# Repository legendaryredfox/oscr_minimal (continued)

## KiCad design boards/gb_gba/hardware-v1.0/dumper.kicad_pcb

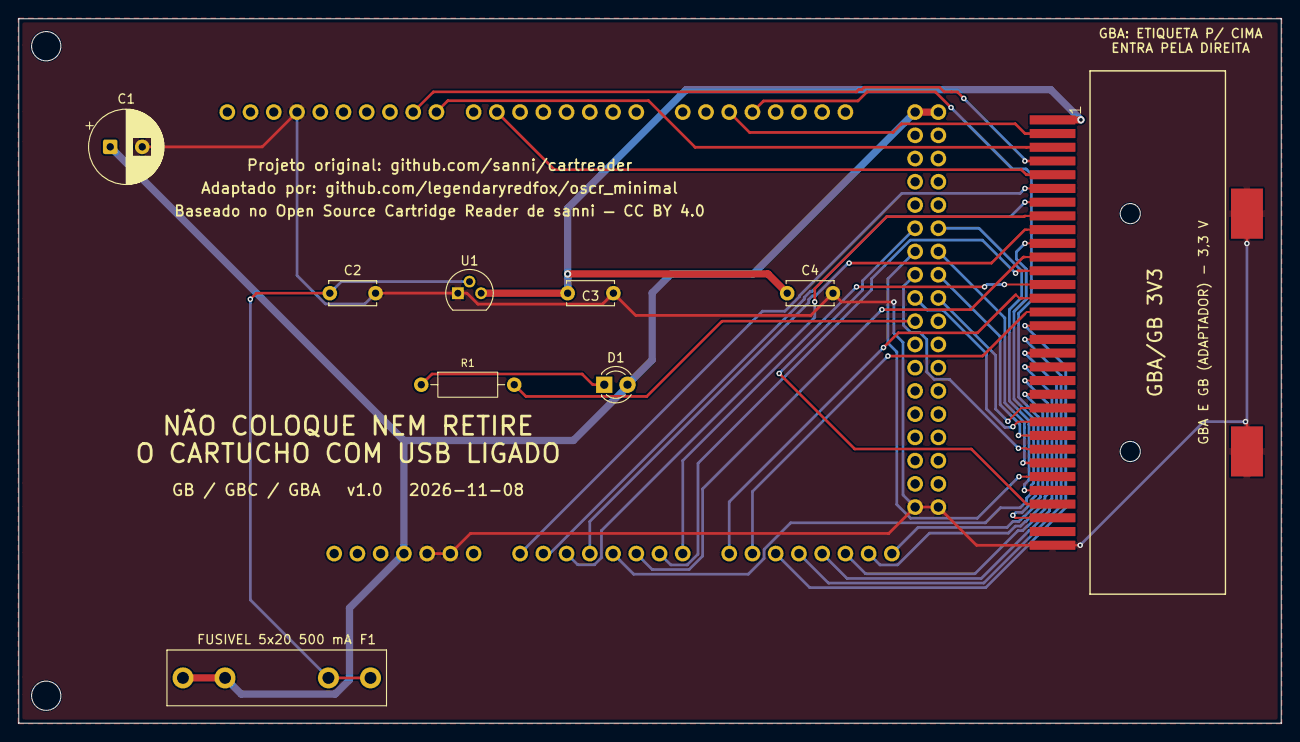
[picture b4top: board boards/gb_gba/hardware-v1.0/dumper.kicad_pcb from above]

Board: 2 copper layers, 138.0 x 77.0 mm, 12 parts (0 on the bottom side), 35 nets.

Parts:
A1: Mega2560_R3_Shield
C1: 470u/16V; CP_Radial_D8.0mm_P3.50mm
C2, C3: 1u; C_Disc_D5.0mm_W2.5mm_P5.00mm
C4: 100n; C_Disc_D5.0mm_W2.5mm_P5.00mm
D1: LED 3mm; LED_D3.0mm
F1: Fusivel 5x20 500mA; Fuseholder_Littelfuse_100_series_5x20mm
GBA1: GBA_Slot
MH1, MH3: MountingHole_3.2mm; MountingHole_3.2mm_M3
R1: 220R; R_Axial_DIN0207_L6.3mm_D2.5mm_P10.16mm_Horizontal
U1: MCP1700-3302E/TO (3,3 V); TO-92

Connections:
+3V3: C3.1, C4.1, GBA1.1, U1.3
+5V: A1.5V1, A1.5V3, A1.5V4, C1.1, D1.2, F1.1
+5V_CART: C2.1, F1.2, U1.2
/A0: A1.A0, GBA1.6
/A1: A1.A1, GBA1.7
/A2: A1.A2, GBA1.8
/A3: A1.A3, GBA1.9
/A4: A1.A4, GBA1.10
/A5: A1.A5, GBA1.11
/A6: A1.A6, GBA1.12
/A7: A1.A7, GBA1.13
/A8: A1.A8, GBA1.14
/A9: A1.A9, GBA1.15
/A10: A1.A10, GBA1.16
/A11: A1.A11, GBA1.17
/A12: A1.A12, GBA1.18
/A13: A1.A13, GBA1.19
/A14: A1.A14, GBA1.20
/A15: A1.A15, GBA1.21
/D6: A1.D6, GBA1.5
/D8: A1.D8, GBA1.3
/D9: A1.D9, GBA1.4
/D16: A1.D16, GBA1.2
/D17: A1.D17, GBA1.30
/D30: A1.D30, GBA1.29
/D31: A1.D31, GBA1.28
/D32: A1.D32, GBA1.27
/D33: A1.D33, GBA1.26
/D34: A1.D34, GBA1.25
/D35: A1.D35, GBA1.24
/D36: A1.D36, GBA1.23
/D37: A1.D37, GBA1.22
GND: A1.GND1, A1.GND2, A1.GND3, A1.GND5, A1.GND6, C1.2, C2.2, C3.2, C4.2, GBA1.32, GBA1.SHIELD_3, GBA1.SHIELD_4, U1.1
unnamed: A1.D38, R1.2
unnamed: D1.1, R1.1

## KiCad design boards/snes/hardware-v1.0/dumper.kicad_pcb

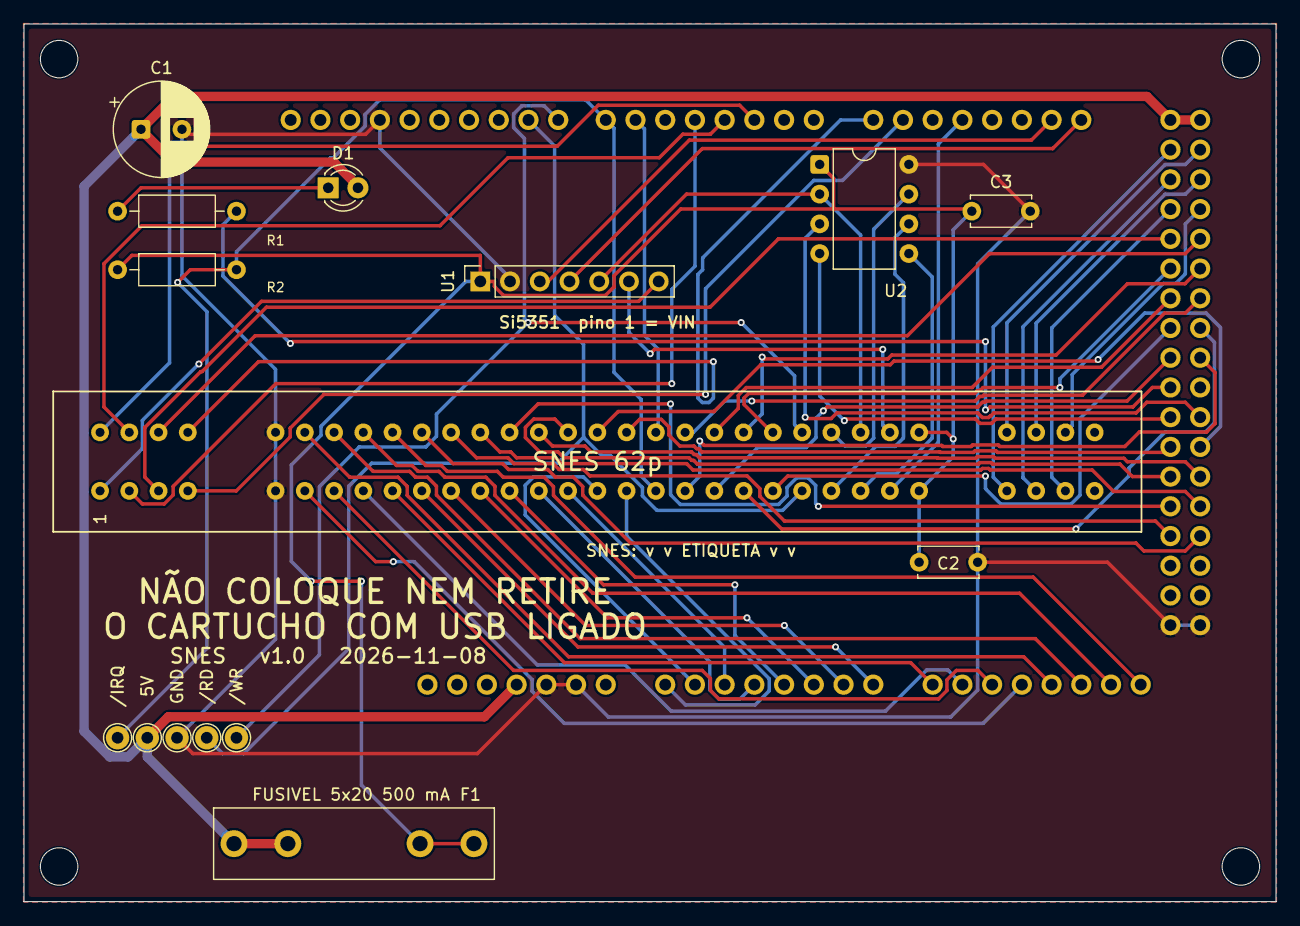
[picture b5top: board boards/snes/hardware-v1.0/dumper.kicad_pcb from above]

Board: 2 copper layers, 107.0 x 75.0 mm, 20 parts (0 on the bottom side), 65 nets.

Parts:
A1: Mega2560_R3_Shield
C1: 470u/16V; CP_Radial_D8.0mm_P3.50mm
C2, C3: 100n; C_Disc_D5.0mm_W2.5mm_P5.00mm
D1: LED 3mm; LED_D3.0mm
F1: Fusivel 5x20 500mA; Fuseholder_Littelfuse_100_series_5x20mm
MH1, MH2, MH3, MH4: MountingHole_3.2mm; MountingHole_3.2mm_M3
R1: 220R; R_Axial_DIN0207_L6.3mm_D2.5mm_P10.16mm_Horizontal
R2: 1k; R_Axial_DIN0207_L6.3mm_D2.5mm_P10.16mm_Horizontal
SNES1: SNES_Slot
TP1: 5V; TestPoint_THTPad_D2.0mm_Drill1.0mm
TP2: GND; TestPoint_THTPad_D2.0mm_Drill1.0mm
TP3: /RD; TestPoint_THTPad_D2.0mm_Drill1.0mm
TP4: /WR; TestPoint_THTPad_D2.0mm_Drill1.0mm
TP5: /IRQ; TestPoint_THTPad_D2.0mm_Drill1.0mm
U1: Si5351_Module; PinSocket_1x07_P2.54mm_Vertical
U2: PIC12F629 (em soquete; snescic-lock-resync); DIP-8_W7.62mm

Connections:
+5V: A1.5V1, A1.5V3, A1.5V4, C1.1, D1.2, F1.1, TP1.1
+5V_CART: C2.1, C3.1, F1.2, R2.1, SNES1.27, SNES1.58, U1.1, U2.1
/A0: A1.A0, SNES1.17
/A1: A1.A1, SNES1.16
/A2: A1.A2, SNES1.15
/A3: A1.A3, SNES1.14
/A4: A1.A4, SNES1.13
/A5: A1.A5, SNES1.12
/A6: A1.A6, SNES1.11
/A7: A1.A7, SNES1.10
/A8: A1.A8, SNES1.9
/A9: A1.A9, SNES1.8
/A10: A1.A10, SNES1.7
/A11: A1.A11, SNES1.6
/A12: A1.A12, SNES1.37
/A13: A1.A13, SNES1.38
/A14: A1.A14, SNES1.39
/A15: A1.A15, SNES1.40
/CIC_DATA_0: SNES1.55, U2.7
/CIC_DATA_1: SNES1.24, U2.6
/CIC_RESET: SNES1.25, U2.5
/CLK0: SNES1.1, U1.7
/CLK1: SNES1.57, U1.6
/CLK2: SNES1.56, U1.5, U2.2
/D2: A1.D2, SNES1.32
/D3: A1.D3, SNES1.33
/D4: A1.D4, SNES1.2
/D6: A1.D6, SNES1.49
/D7: A1.D7, R2.2, SNES1.18, TP5.1
/D8: A1.D8, SNES1.54, TP4.1
/D9: A1.D9, SNES1.23, TP3.1
/D14: A1.D14, SNES1.35
/D15: A1.D15, SNES1.4
/D17: A1.D17, SNES1.26
/D22: A1.D22, SNES1.28
/D23: A1.D23, SNES1.59
/D24: A1.D24, SNES1.29
/D25: A1.D25, SNES1.60
/D26: A1.D26, SNES1.30
/D27: A1.D27, SNES1.61
/D28: A1.D28, SNES1.3
/D29: A1.D29, SNES1.34
/D30: A1.D30, SNES1.53
/D31: A1.D31, SNES1.52
/D32: A1.D32, SNES1.51
/D33: A1.D33, SNES1.50
/D34: A1.D34, SNES1.22
/D35: A1.D35, SNES1.21
/D36: A1.D36, SNES1.20
/D37: A1.D37, SNES1.19
/D42: A1.D42, SNES1.48
/D43: A1.D43, SNES1.47
/D44: A1.D44, SNES1.46
/D45: A1.D45, SNES1.45
/D46: A1.D46, SNES1.44
/D47: A1.D47, SNES1.43
/D48: A1.D48, SNES1.42
/D49: A1.D49, SNES1.41
GND: A1.GND1, A1.GND2, A1.GND3, A1.GND5, A1.GND6, C1.2, C2.2, C3.2, SNES1.5, SNES1.36, TP2.1, U1.2, U2.8
unnamed: A1.D38, R1.2
unnamed: D1.1, R1.1
unnamed: A1.D21, U1.4
unnamed: A1.D20, U1.3
unnamed: A1.D40, U2.4
unnamed: A1.D41, U2.3

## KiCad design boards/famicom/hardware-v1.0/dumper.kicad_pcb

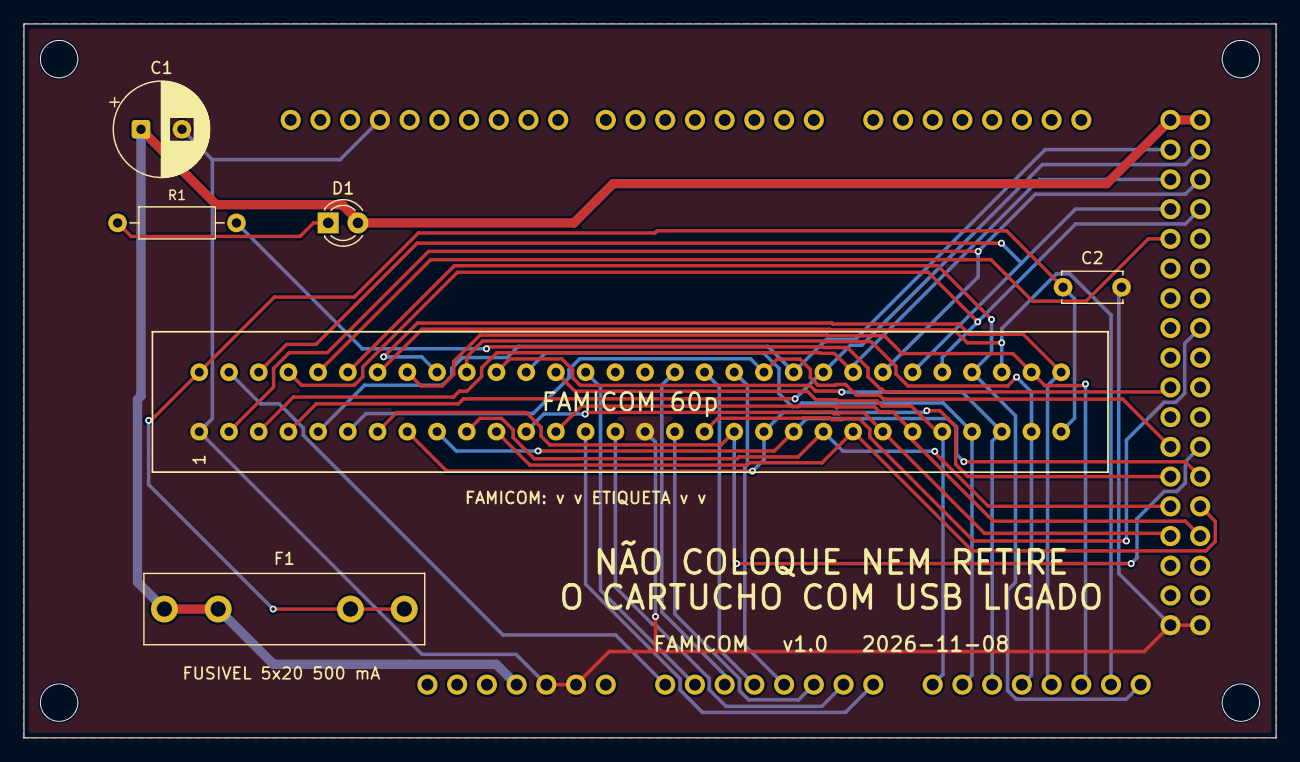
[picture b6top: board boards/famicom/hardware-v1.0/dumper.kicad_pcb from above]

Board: 2 copper layers, 107.0 x 61.0 mm, 11 parts (0 on the bottom side), 37 nets.

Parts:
A1: Mega2560_R3_Shield
C1: 470u/16V; CP_Radial_D8.0mm_P3.50mm
C2: 100n; C_Disc_D5.0mm_W2.5mm_P5.00mm
D1: LED 3mm; LED_D3.0mm
F1: Fusivel 5x20 500mA; Fuseholder_Littelfuse_100_series_5x20mm
FC1: FC_Slot
MH1, MH2, MH3, MH4: MountingHole_3.2mm; MountingHole_3.2mm_M3
R1: 220R; R_Axial_DIN0207_L6.3mm_D2.5mm_P10.16mm_Horizontal

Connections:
+5V: A1.5V1, A1.5V3, A1.5V4, C1.1, D1.2, F1.1
+5V_CART: C2.1, F1.2, FC1.30, FC1.31
/A0: A1.A0, FC1.32
/A1: A1.A1, FC1.44
/A2: A1.A2, FC1.47
/A3: A1.A3, FC1.48
/A4: A1.A4, FC1.49
/A5: A1.A5, FC1.17
/A6: A1.A6, FC1.15
/A7: A1.A7, FC1.14
/A8: A1.A8, FC1.26, FC1.43
/A9: A1.A9, FC1.27, FC1.42
/A10: A1.A10, FC1.28, FC1.41
/A11: A1.A11, FC1.29, FC1.40
/A12: A1.A12, FC1.39, FC1.60
/A13: A1.A13, FC1.38, FC1.59
/A14: A1.A14, FC1.37, FC1.58
/A15: A1.A15, FC1.36, FC1.57
/D22: A1.D22, FC1.5, FC1.51
/D23: A1.D23, FC1.4, FC1.52
/D24: A1.D24, FC1.3, FC1.53
/D25: A1.D25, FC1.2, FC1.54
/D26: A1.D26, FC1.33, FC1.55
/D27: A1.D27, FC1.34, FC1.56
/D28: A1.D28, FC1.35
/D35: A1.D35, FC1.18
/D42: A1.D42, FC1.6, FC1.50
/D43: A1.D43, FC1.7, FC1.19
/D44: A1.D44, FC1.8, FC1.20
/D45: A1.D45, FC1.9, FC1.21
/D46: A1.D46, FC1.10, FC1.22
/D47: A1.D47, FC1.11, FC1.23
/D48: A1.D48, FC1.12, FC1.24
/D49: A1.D49, FC1.13, FC1.25
GND: A1.GND1, A1.GND2, A1.GND3, A1.GND5, A1.GND6, C1.2, C2.2, FC1.1, FC1.16
unnamed: A1.D38, R1.2
unnamed: D1.1, R1.1

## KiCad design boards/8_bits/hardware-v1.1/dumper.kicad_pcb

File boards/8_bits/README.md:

# 8_bits — NES, Famicom e Master System

**README por versão** (renders de cima e de baixo, peças, diferenças): [v1.0](hardware-v1.0/README.md), [v1.1](hardware-v1.1/README.md).

Versão mínima de três slots em shield para Arduino Mega 2560 R3, 100% THT, só USB: **NES** (72p, 2,5 mm), **Famicom** (60p, 2,54 mm) e **Master System / Mark III** (50p, 2,54 mm). Os três slots ficam **em paralelo** nos mesmos pinos do Mega (como no `six_slot_adapter` do OSCR): **um cartucho por vez, em um slot só**. Pinagem idêntica ao OSCR HW5 (`docs/pinmap.md`: NES e Famicom da `famicom_nes`, Master System da `megadrive_sms`).

**Si5351, sem PIC:** o NES usa o `CLK0` do Si5351 no pino 37; Famicom e Master System não usam clock (o pino 47 do SMS fica sem ligação, D136). Sem PIC (CIC do SNES), sem R2 e sem regulador de 3,3 V fixo.

## Versões (regra do usuário, 2026-11-11)

- **v1.0: a mínima que funciona, com fusível.** 5V direto nos slots, atrás do F1 (suporte de fusível 5×20 mm de 500 mA, D144). 117,1 × 97,1 mm.
- **v1.1: proteção mais robusta.** A v1.0 mais o seletor de tensão 3,3 V/5 V nos três slots (LDO LD1117V33, Q1 de bypass, Q2 de comando pelo D18; D138, D147) e o J1 "TRAVA 3,3 V". 117,1 × 109,1 mm. Firmware: ambiente `SerialASCII_Volt`.

O 5V dos slots **não é cortado por software** em nenhuma versão (D139): para trocar o cartucho, desligue o USB.

**Estado:** ERC 0 violações; DRC sem ligações abertas nem erros (só avisos de biblioteca); netlist confere com `docs/pinmap.md` nas duas versões (`tools/check_netlist.py --board 8_bits`). Roteadas pelo Freerouting e costuradas com vias de GND: **revisar o layout no KiCad antes de encomendar**. Nada encomendado, montado nem testado.

## Como foi feita (D153)

Criada da `famicom_nes` (v1.0 para a v1.0, v1.1 para a v1.1) com o slot SMS acrescentado, a mesma receita da `megadrive_sms` (D136). Scripts em `tools/boards/8_bits/` (da raiz do repositório):

1. `add_sms_sch.py` acrescenta SMS1 e o capacitor do slot ao esquemático, tira as marcas de não conexão dos 11 pinos do Mega que só o SMS usa (D6, D8, D9, D17, D30 a D34, D36, D37) e põe os rótulos. Variáveis `SMS_VCC` (`+5V_CART` na v1.0, `VCC_CART` na v1.1), `SMS_CAP` e `SMS_CAP_SRC`.
2. `place_sms.py` (python com `pcbnew`) tira trilhas e zonas, acrescenta SMS1 e o capacitor, liga os pads do Mega às nets novas; na v1.0 estende a placa para baixo (127 para 135 mm).
3. `renum.py` (v1.1) e `renum_pwr.py` deixam as referências em sequência: C4 (SMS), C5 e C6 (LDO), R2 a R4, Q1 e Q2, e os `#PWR` (D109, D150).
4. `reroute.sh` (`VER=v1.0|v1.1`): Freerouting, zonas de GND, costura e preenchimento; depois `tools/troca/pads_solidos.py` onde o DRC acusa `starved_thermal`.

```
python3 tools/check_netlist.py --board 8_bits                                              # v1.1
python3 tools/check_netlist.py --board 8_bits boards/8_bits/hardware-v1.0/dumper.kicad_sch  # v1.0
kicad-cli sch erc boards/8_bits/hardware-v1.1/dumper.kicad_sch
kicad-cli pcb drc boards/8_bits/hardware-v1.1/dumper.kicad_pcb
tools/export_fab.sh 8_bits v1.1
```

## Pendências

1. **Direção da etiqueta do cartucho SMS** no silk (não confirmada; NES e Famicom estão).
2. Medidas dos três slots comprados e do módulo Si5351; folga entre o SMS e os furos de canto de baixo (v1.0: 0,3 mm de folga de caixa).
3. **Firmware:** o núcleo `SMS.cpp` está ligado no fork (D137) mas nunca rodou em hardware; o slot SMS desta placa é o `--mapper 0`.
4. Revisar o layout no KiCad (autoroteador).
5. Sem furos de fixação no Mega (só os 4 de canto): a força de inserir o cartucho passa pelos pinos dos headers.

**Peças opcionais:** [`docs/bom.md`](docs/bom.md). BOM: [`docs/bom.md`](docs/bom.md). Montagem: [`docs/montagem.md`](docs/montagem.md).

Atribuição: baseado no Open Source Cartridge Reader de sanni (CC BY 4.0).

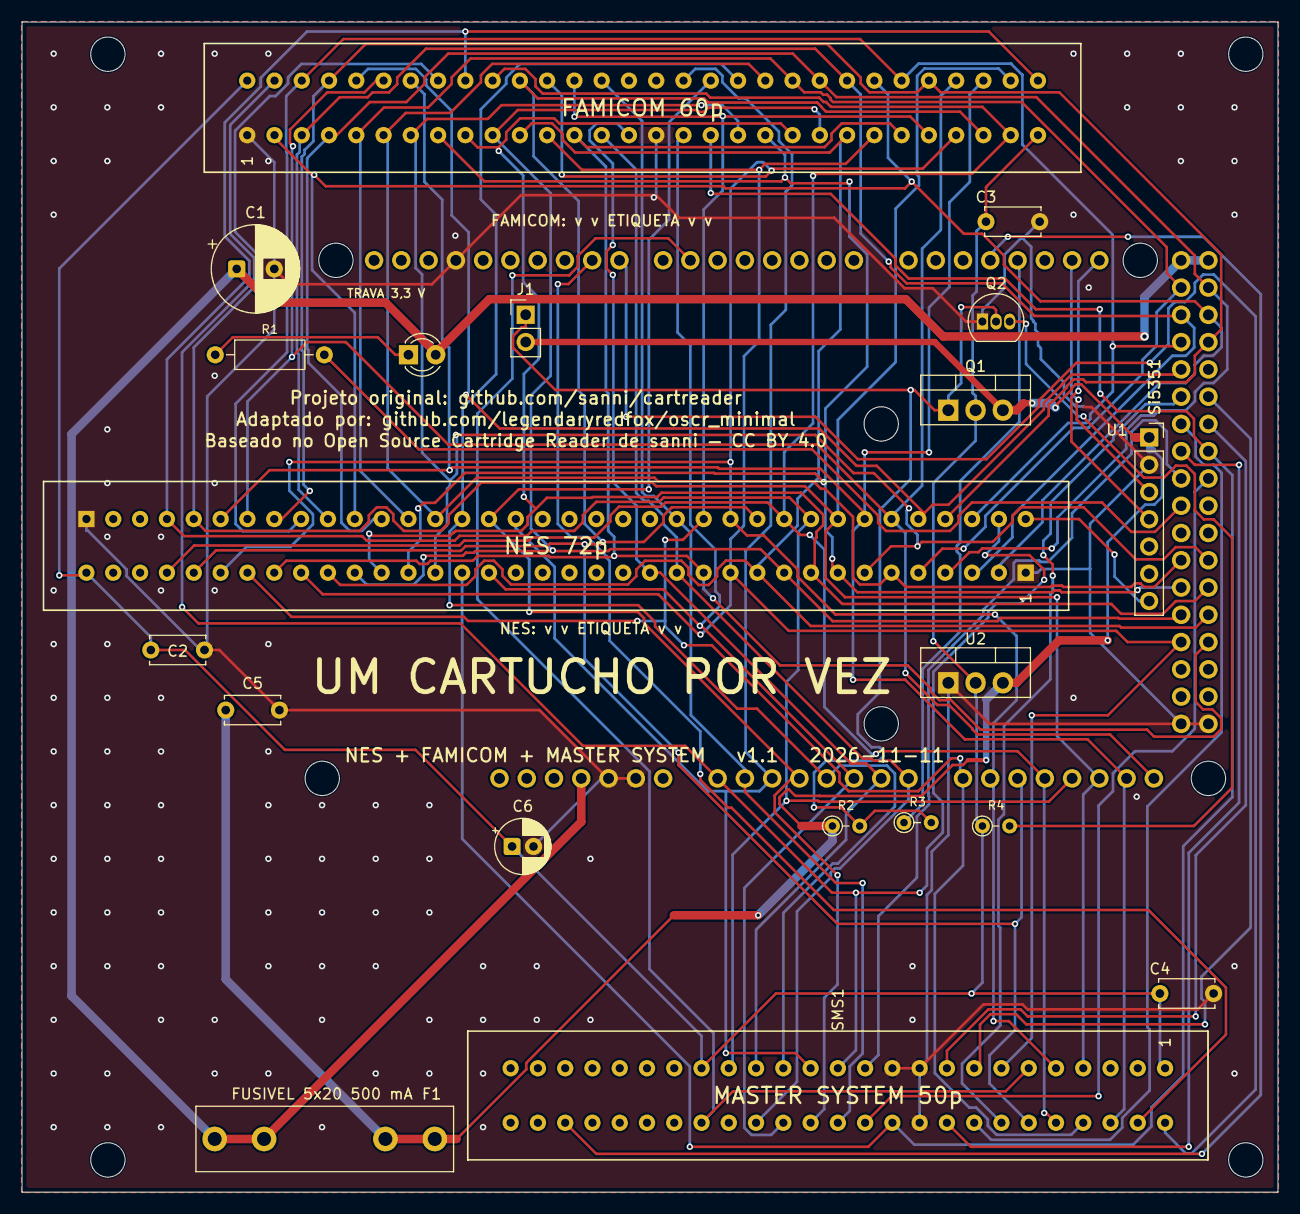
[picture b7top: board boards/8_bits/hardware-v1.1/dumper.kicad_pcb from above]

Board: 2 copper layers, 117.0 x 109.0 mm, 25 parts (0 on the bottom side), 55 nets.

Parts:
A1: Mega2560_R3_Shield
C1: 470u/16V; CP_Radial_D8.0mm_P3.50mm
C2, C3, C4, C5: 100n; C_Disc_D5.0mm_W2.5mm_P5.00mm
C6: 10u/16V; CP_Radial_D5.0mm_P2.00mm
D1: LED 3mm; LED_D3.0mm
F1: Fusivel 5x20 500mA; Fuseholder_Littelfuse_100_series_5x20mm
FC1: FC_Slot
J1: TRAVA 3,3 V; PinHeader_1x02_P2.54mm_Vertical
MH1, MH2, MH3, MH4: MountingHole_3.2mm; MountingHole_3.2mm_M3
NES1: NES_Slot
Q1: IRF9540N; TO-220-3_Vertical
Q2: 2N7000; TO-92_Inline
R1: 220R; R_Axial_DIN0207_L6.3mm_D2.5mm_P10.16mm_Horizontal
R2: 100k; R_Axial_DIN0204_L3.6mm_D1.6mm_P2.54mm_Vertical
R3: 1k; R_Axial_DIN0204_L3.6mm_D1.6mm_P2.54mm_Vertical
R4: 220R; R_Axial_DIN0204_L3.6mm_D1.6mm_P2.54mm_Vertical
SMS1: SMS_Slot
U1: Si5351_Module; PinSocket_1x07_P2.54mm_Vertical
U2: LD1117V33; TO-220-3_Vertical

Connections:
+5V: A1.5V1, A1.5V3, A1.5V4, C1.1, D1.2, F1.1
+5V_CART: C5.1, F1.2, J1.2, Q1.3, R2.1, U1.1, U2.3
/A0: A1.A0, FC1.32, NES1.38, SMS1.25
/A1: A1.A1, FC1.44, NES1.50, SMS1.26
/A2: A1.A2, FC1.47, NES1.56, SMS1.27
/A3: A1.A3, FC1.48, NES1.57, SMS1.28
/A4: A1.A4, FC1.49, NES1.58, SMS1.29
/A5: A1.A5, FC1.17, NES1.21, SMS1.30
/A6: A1.A6, FC1.15, NES1.15, SMS1.31
/A7: A1.A7, FC1.14, NES1.14, SMS1.32
/A8: A1.A8, FC1.26, FC1.43, NES1.30, NES1.49, SMS1.8
/A9: A1.A9, FC1.27, FC1.42, NES1.31, NES1.48, SMS1.9
/A10: A1.A10, FC1.28, FC1.41, NES1.32, NES1.47, SMS1.12
/A11: A1.A11, FC1.29, FC1.40, NES1.33, NES1.46, SMS1.10
/A12: A1.A12, FC1.39, FC1.60, NES1.45, NES1.69, SMS1.33
/A13: A1.A13, FC1.38, FC1.59, NES1.44, NES1.68, SMS1.7
/A14: A1.A14, FC1.37, FC1.58, NES1.43, NES1.67, SMS1.6
/A15: A1.A15, FC1.36, FC1.57, NES1.42, NES1.66
/CLK0: NES1.37, U1.7
/D6: A1.D6, SMS1.11, SMS1.36
/D8: A1.D8, SMS1.2
/D9: A1.D9, SMS1.4
/D17: A1.D17, SMS1.46
/D22: A1.D22, FC1.5, FC1.51, NES1.5, NES1.60
/D23: A1.D23, FC1.4, FC1.52, NES1.4, NES1.61
/D24: A1.D24, FC1.3, FC1.53, NES1.3, NES1.63
/D25: A1.D25, FC1.2, FC1.54, NES1.2, NES1.62
/D26: A1.D26, FC1.33, FC1.55, NES1.39, NES1.64
/D27: A1.D27, FC1.34, FC1.56, NES1.40, NES1.65
/D28: A1.D28, FC1.35, NES1.41
/D30: A1.D30, SMS1.14
/D31: A1.D31, SMS1.15
/D32: A1.D32, SMS1.16
/D33: A1.D33, SMS1.17
/D34: A1.D34, SMS1.18
/D35: A1.D35, FC1.18, NES1.22, SMS1.22
/D36: A1.D36, SMS1.23
/D37: A1.D37, SMS1.24
/D42: A1.D42, FC1.6, FC1.50, NES1.6, NES1.59
/D43: A1.D43, FC1.7, FC1.19, NES1.7, NES1.23
/D44: A1.D44, FC1.8, FC1.20, NES1.8, NES1.24
/D45: A1.D45, FC1.9, FC1.21, NES1.9, NES1.25
/D46: A1.D46, FC1.10, FC1.22, NES1.10, NES1.26
/D47: A1.D47, FC1.11, FC1.23, NES1.11, NES1.27
/D48: A1.D48, FC1.12, FC1.24, NES1.12, NES1.28, SMS1.13
/D49: A1.D49, FC1.13, FC1.25, NES1.13, NES1.29
/VSEL_EN: A1.D18, R3.1
/VSEL_G: J1.1, Q1.1, Q2.2, R2.2, R3.2
GND: A1.GND1, A1.GND2, A1.GND3, A1.GND5, A1.GND6, C1.2, C2.2, C3.2, C4.2, C5.2, C6.2, FC1.1, FC1.16, NES1.1, NES1.72, Q2.1, SMS1.19, SMS1.20, SMS1.21, U1.2, U2.1
unnamed: A1.D38, R1.2
unnamed: D1.1, R1.1
unnamed: Q2.3, R4.2
unnamed: A1.D21, U1.4
unnamed: A1.D20, U1.3
VCC_CART: C2.1, C3.1, C4.1, C6.1, FC1.30, FC1.31, NES1.36, Q1.2, R4.1, SMS1.1, SMS1.35, U2.2

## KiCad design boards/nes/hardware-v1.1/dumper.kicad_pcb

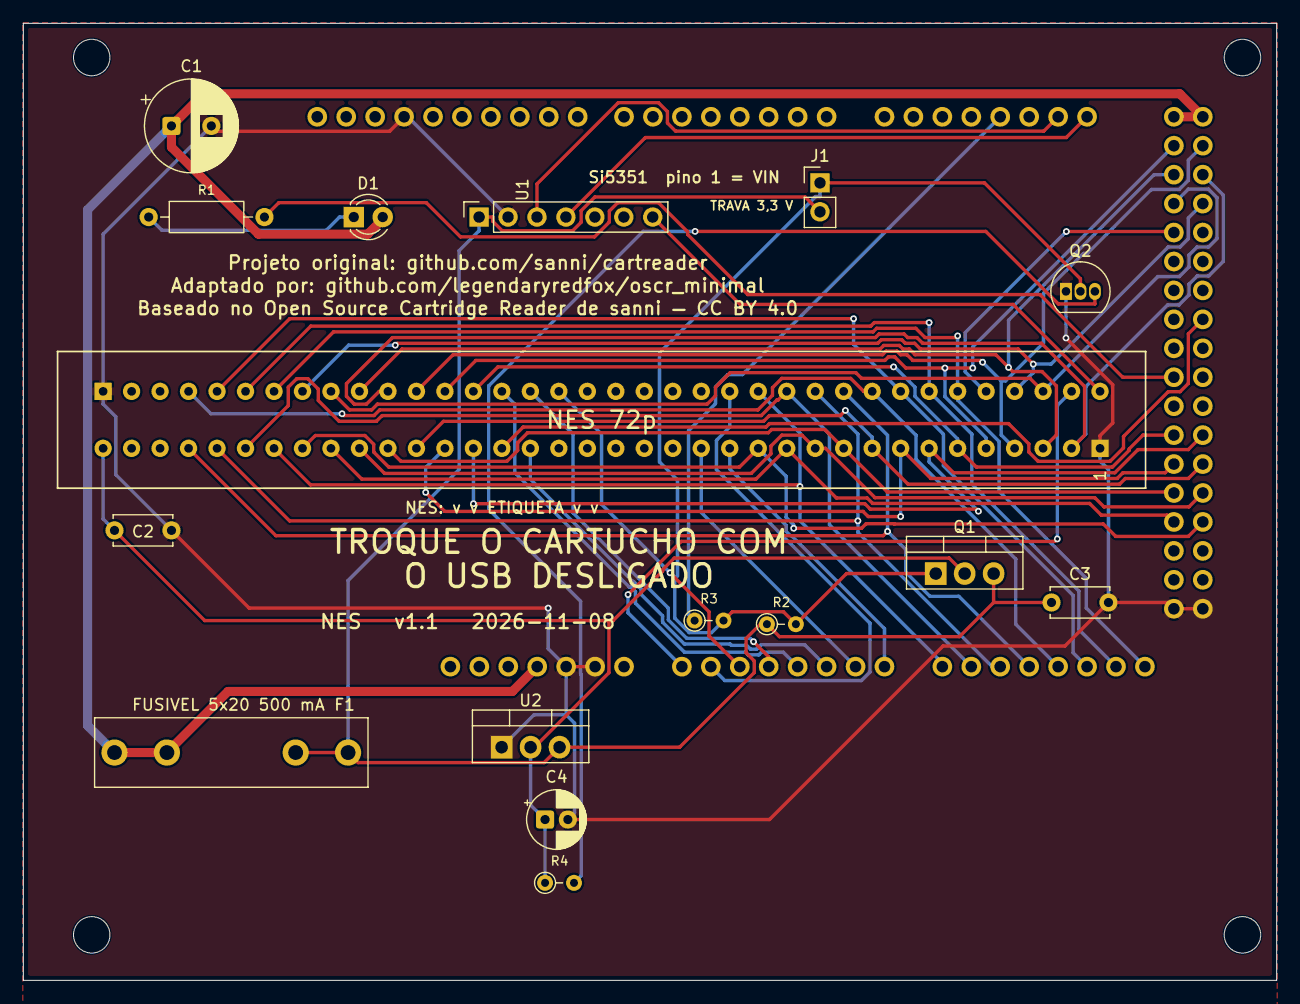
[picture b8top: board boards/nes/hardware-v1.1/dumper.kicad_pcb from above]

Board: 2 copper layers, 110.0 x 84.0 mm, 21 parts (0 on the bottom side), 44 nets.

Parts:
A1: Mega2560_R3_Shield
C1: 470u/16V; CP_Radial_D8.0mm_P3.50mm
C2, C3: 100n; C_Disc_D5.0mm_W2.5mm_P5.00mm
C4: 10u/16V; CP_Radial_D5.0mm_P2.00mm
D1: LED 3mm; LED_D3.0mm
F1: Fusivel 5x20 500mA; Fuseholder_Littelfuse_100_series_5x20mm
J1: TRAVA 3,3 V; PinHeader_1x02_P2.54mm_Vertical
MH1, MH2, MH3, MH4: MountingHole_3.2mm; MountingHole_3.2mm_M3
NES1: NES_Slot
Q1: IRF9540N; TO-220-3_Vertical
Q2: 2N7000; TO-92_Inline
R1: 220R; R_Axial_DIN0207_L6.3mm_D2.5mm_P10.16mm_Horizontal
R2: 100k; R_Axial_DIN0204_L3.6mm_D1.6mm_P2.54mm_Vertical
R3: 1k; R_Axial_DIN0204_L3.6mm_D1.6mm_P2.54mm_Vertical
R4: 220R; R_Axial_DIN0204_L3.6mm_D1.6mm_P2.54mm_Vertical
U1: Si5351_Module; PinSocket_1x07_P2.54mm_Vertical
U2: LD1117V33; TO-220-3_Vertical

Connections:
+5V: A1.5V1, A1.5V3, A1.5V4, C1.1, D1.2, F1.1
+5V_CART: C3.1, F1.2, J1.2, Q1.3, R2.1, U1.1, U2.3
/A0: A1.A0, NES1.38
/A1: A1.A1, NES1.50
/A2: A1.A2, NES1.56
/A3: A1.A3, NES1.57
/A4: A1.A4, NES1.58
/A5: A1.A5, NES1.21
/A6: A1.A6, NES1.15
/A7: A1.A7, NES1.14
/A8: A1.A8, NES1.30, NES1.49
/A9: A1.A9, NES1.31, NES1.48
/A10: A1.A10, NES1.32, NES1.47
/A11: A1.A11, NES1.33, NES1.46
/A12: A1.A12, NES1.45, NES1.69
/A13: A1.A13, NES1.44, NES1.68
/A14: A1.A14, NES1.43, NES1.67
/A15: A1.A15, NES1.42, NES1.66
/CLK0: NES1.37, U1.7
/D22: A1.D22, NES1.5, NES1.60
/D23: A1.D23, NES1.4, NES1.61
/D24: A1.D24, NES1.3, NES1.63
/D25: A1.D25, NES1.2, NES1.62
/D26: A1.D26, NES1.39, NES1.64
/D27: A1.D27, NES1.40, NES1.65
/D28: A1.D28, NES1.41
/D35: A1.D35, NES1.22
/D42: A1.D42, NES1.6, NES1.59
/D43: A1.D43, NES1.7, NES1.23
/D44: A1.D44, NES1.8, NES1.24
/D45: A1.D45, NES1.9, NES1.25
/D46: A1.D46, NES1.10, NES1.26
/D47: A1.D47, NES1.11, NES1.27
/D48: A1.D48, NES1.12, NES1.28
/D49: A1.D49, NES1.13, NES1.29
/VSEL_EN: A1.D18, R3.1
/VSEL_G: J1.1, Q1.1, Q2.2, R2.2, R3.2
GND: A1.GND1, A1.GND2, A1.GND3, A1.GND5, A1.GND6, C1.2, C2.2, C3.2, C4.2, NES1.1, NES1.72, Q2.1, U1.2, U2.1
unnamed: A1.D38, R1.2
unnamed: D1.1, R1.1
unnamed: Q2.3, R4.2
unnamed: A1.D21, U1.4
unnamed: A1.D20, U1.3
VCC_CART: C2.1, C4.1, NES1.36, Q1.2, R4.1, U2.2

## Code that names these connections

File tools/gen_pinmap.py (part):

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    w("\n## Placa principal — o que o HW5 liga além dos slots (referência)\n")
    w("| item | pino Arduino | fonte |\n|---|---|---|")
    w("| Si5351 SDA / SCL | D20 (PD1) / D21 (PD0) | sch main J7.3/J7.4 + ods |")
    w("| Si5351 CLK0 / CLK1 / CLK2 | 3 saídas do Si5351 (não vão ao Mega); CLK0→SNES 21.477MHz (pino 1), CLK1→SNES CPU clock (57), CLK2→CIC clock (56) e PIC pino 2 | sch |")
    w("| LED de status (cátodo via 220Ω, ânodo em VCC; **ativo em nível baixo**) | D38 (PD7) | sch main D1/R1 + fw `statusLED()` |")
    w("| Pull-up 1kΩ VCC→D7 (linha /IRQ do SNES) | D7 (PH4) | sch six_slot R1 + ods `D7 (1K Pullup)` |")
    w("| Reset do Mega | RESET → J4.35 (adaptadores não usam) | sch main |\n")
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    for net, nodes in pic.items():
        for r, p, fn in nodes:
            if r == "PIC12F629": pm[p] = net
    tgt = {"VCC": "5V", "GND": "GND", "CLK2": "Si5351 CLK2 (mesma net do SNES pino 56)",
           "D40": "Mega D40 (PG1) — Reset In", "D41": "Mega D41 (PG0) — Reset Out Host",
           "CIC RESET": "SNES slot pino 25 (CIC_in_data p7)",
           "CIC DATA 1": "SNES slot pino 24 (CIC_out_data p1)",
           "CIC DATA 0": "SNES slot pino 55 (CIC_data_out p2)"}
    for p in sorted(pm, key=int):
        w(f"| {p} | {pm[p]} | {tgt.get(pm[p], '?')} | sch(PIC_adapter + six_slot JCIC1) + ods(snesCIC) + fw SNES.ino (PG0/PG1) |")
    w("\nNota: o PIC12F629 usa a pinagem do `JCIC1` (1=VCC, 2=CLK2, 3=D41, 4=D40, 5=RESET, 6=DATA1, 7=DATA0, 8=GND).\n")
    w("## Pinos do slot sem ligação no OSCR (mantidos sem ligação)\n")
    w("- SNES: pino 31 (Left Audio), pino 62 (Right Audio).")
    w("- NES: `EXP_0..EXP_9` (16-20, 51-55), `Security1..4` (70, 71, 34, 35).")
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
